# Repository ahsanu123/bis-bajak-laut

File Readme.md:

<p  align="center">    

  <br/>
  <b>Bis Bajak Laut</b> is a Copy of <a href="https://docs.buspirate.com/">Bus Pirate</a>
</p> 

# 🍿 Hardware

## 🌳 Log

- 10 Oktober 2025, 19:30, start date.

## 🧰 References

- [bus pirate hardware documentation](https://docs.buspirate.com/docs/overview/hardware/)

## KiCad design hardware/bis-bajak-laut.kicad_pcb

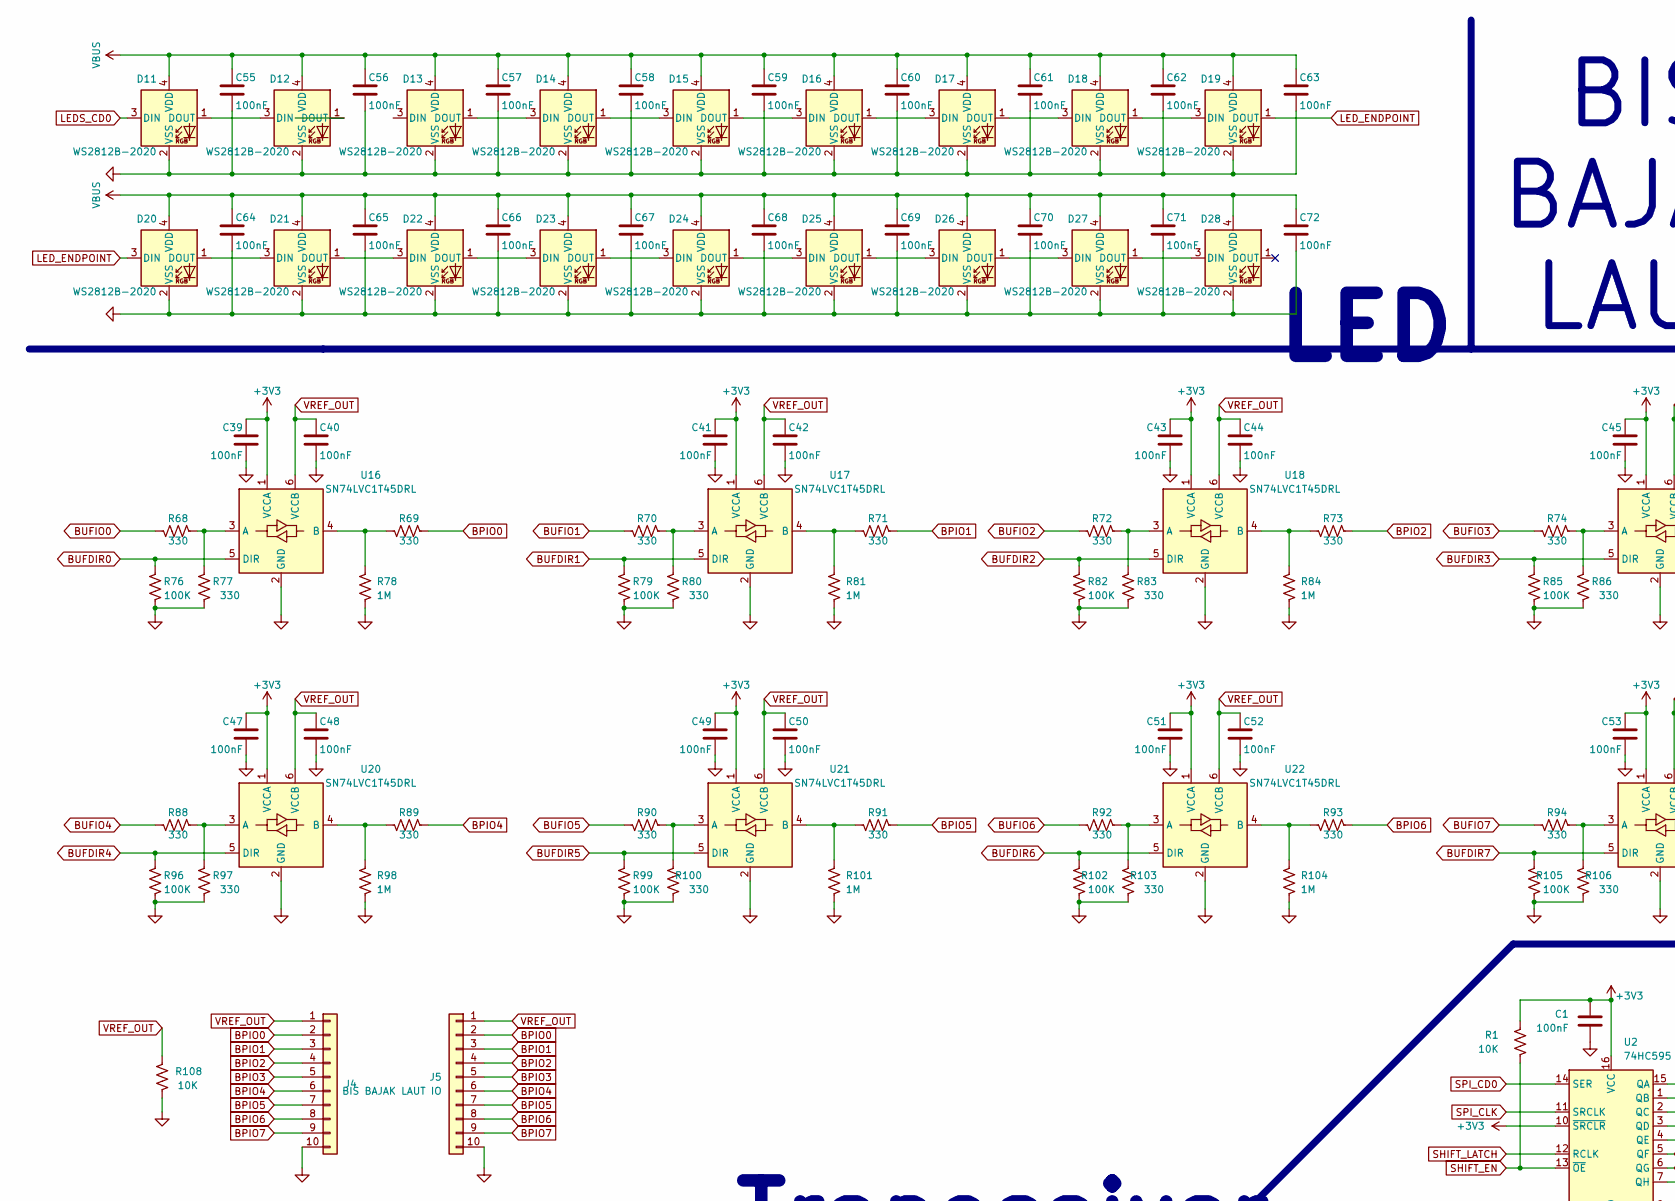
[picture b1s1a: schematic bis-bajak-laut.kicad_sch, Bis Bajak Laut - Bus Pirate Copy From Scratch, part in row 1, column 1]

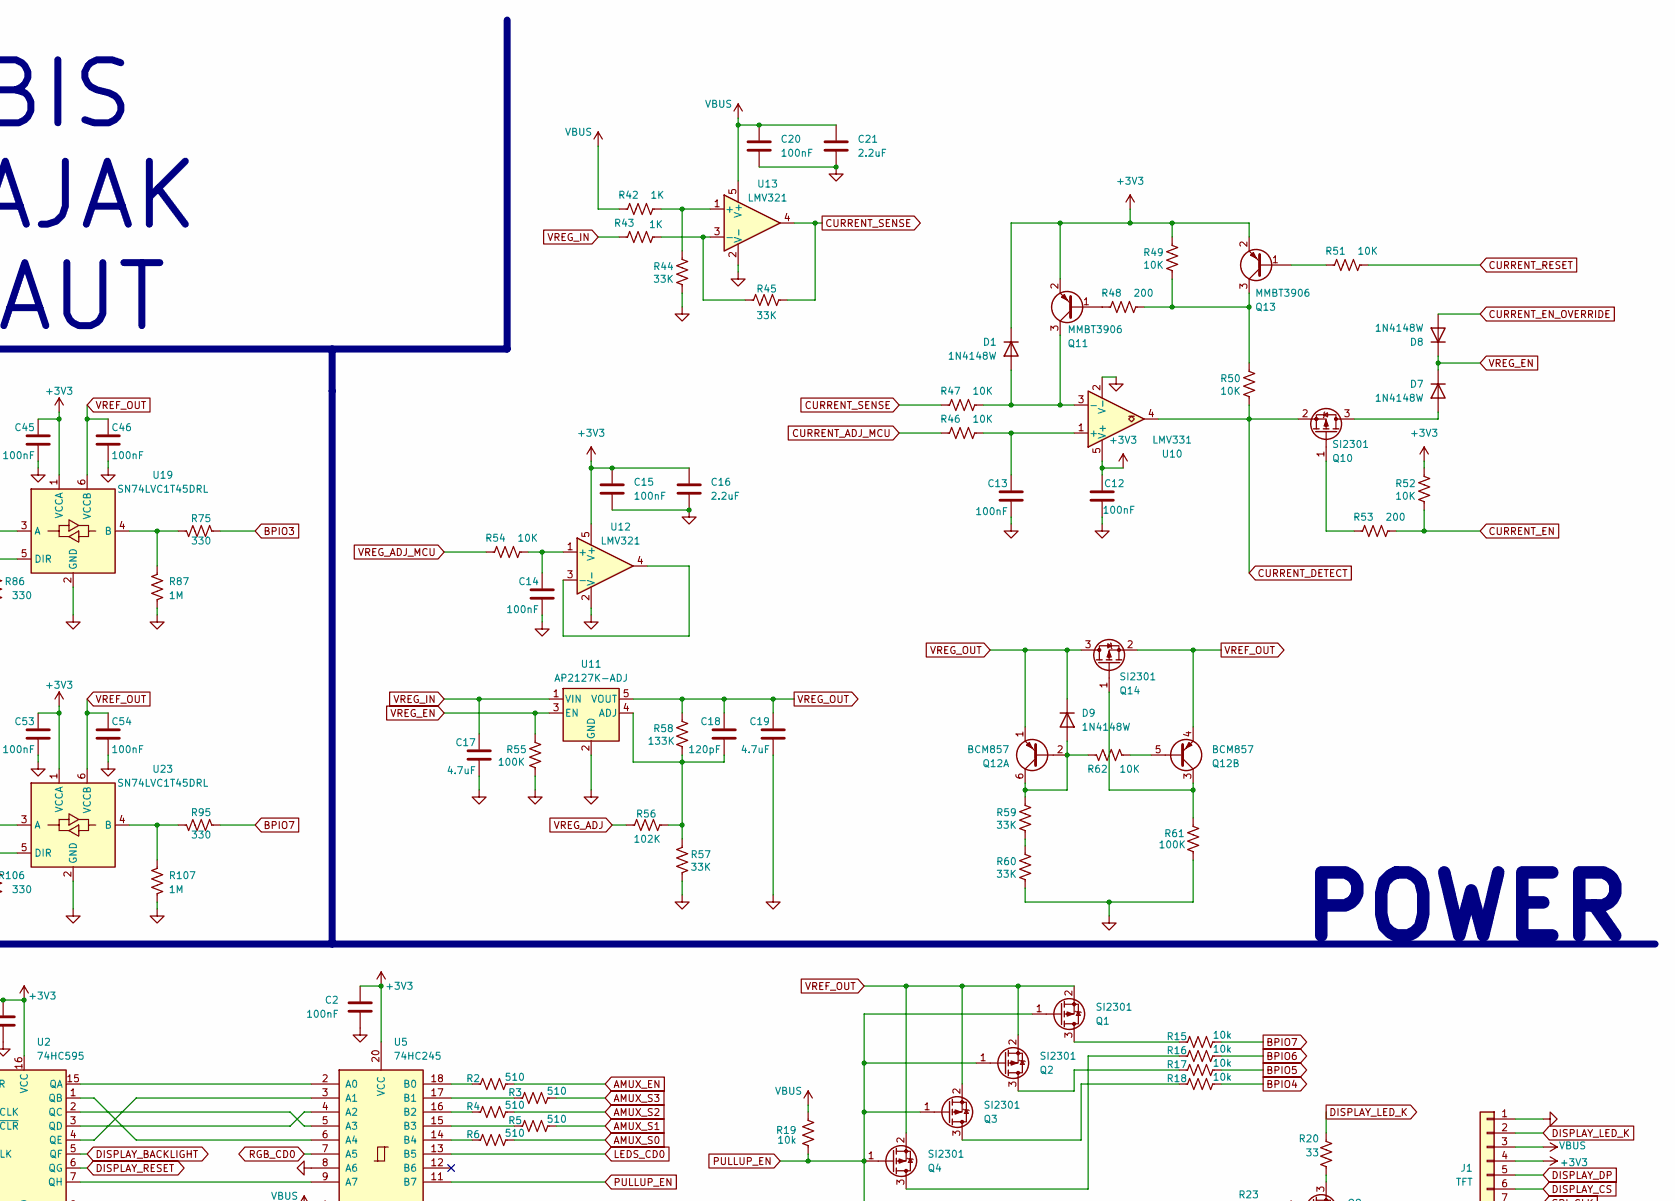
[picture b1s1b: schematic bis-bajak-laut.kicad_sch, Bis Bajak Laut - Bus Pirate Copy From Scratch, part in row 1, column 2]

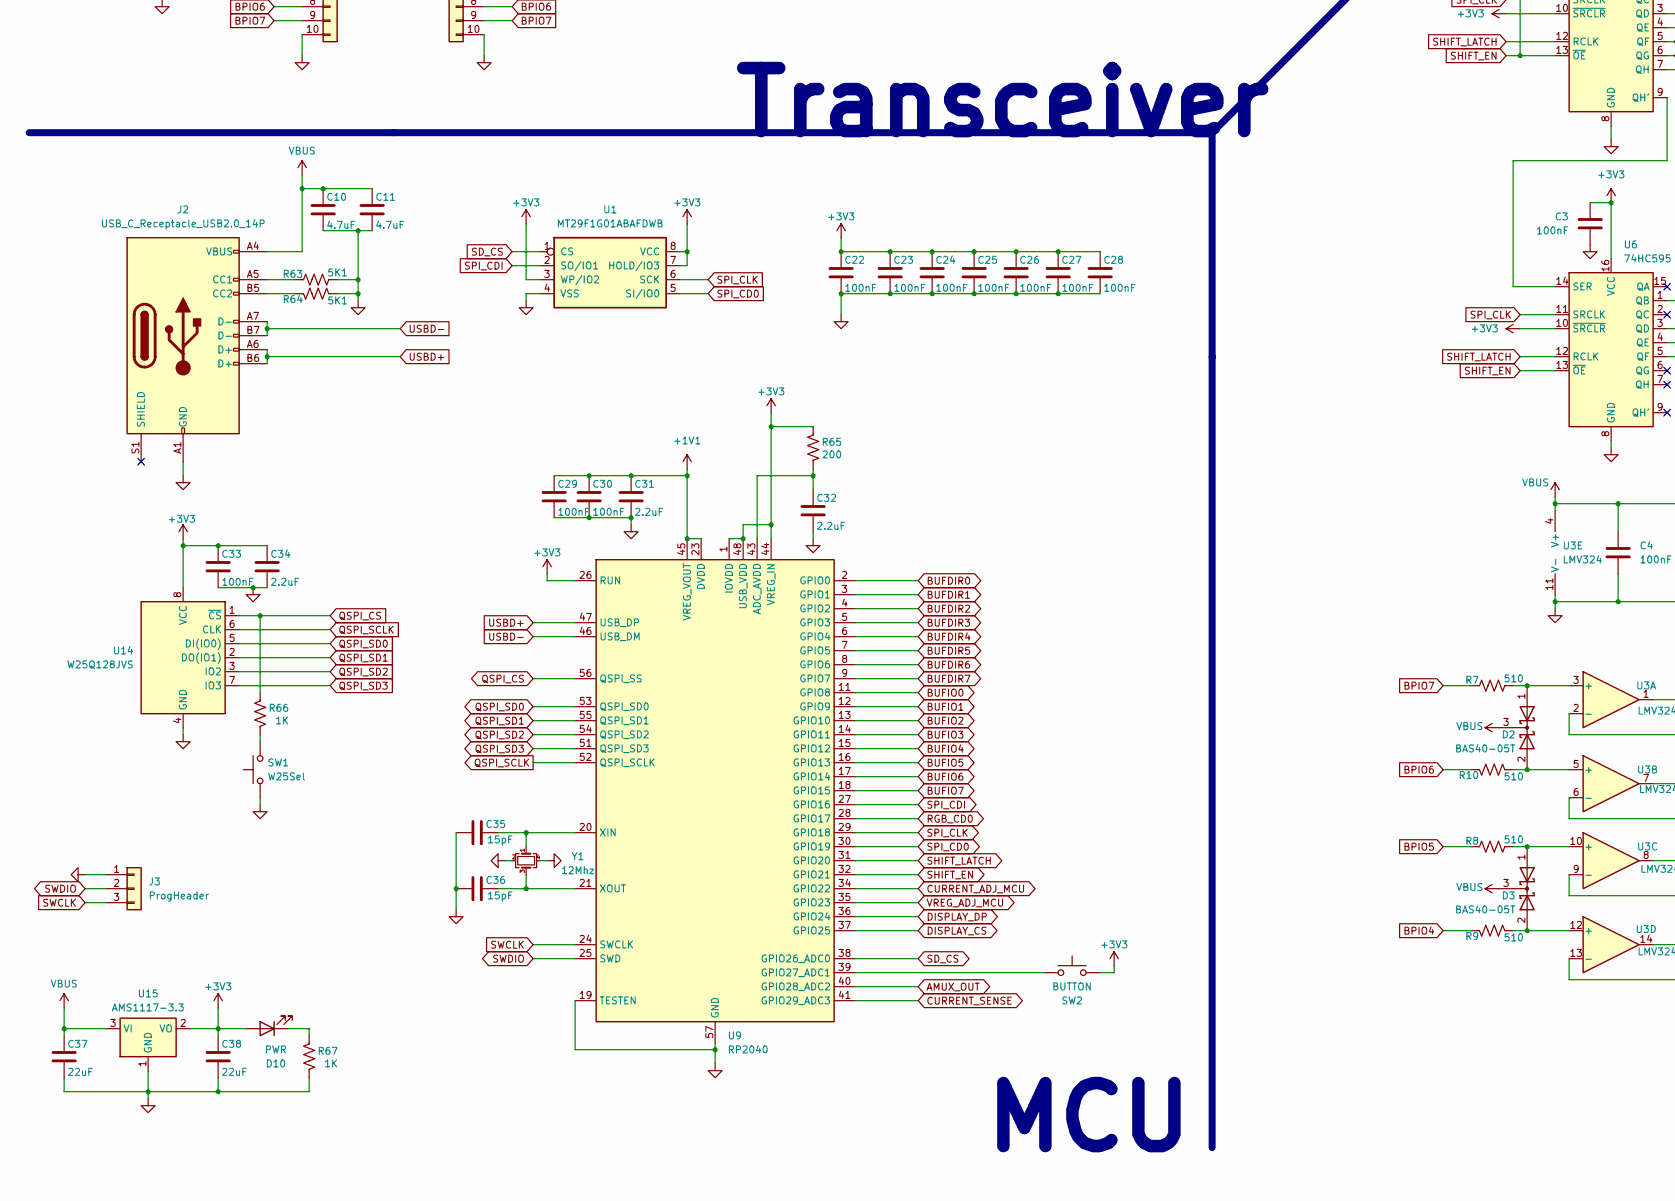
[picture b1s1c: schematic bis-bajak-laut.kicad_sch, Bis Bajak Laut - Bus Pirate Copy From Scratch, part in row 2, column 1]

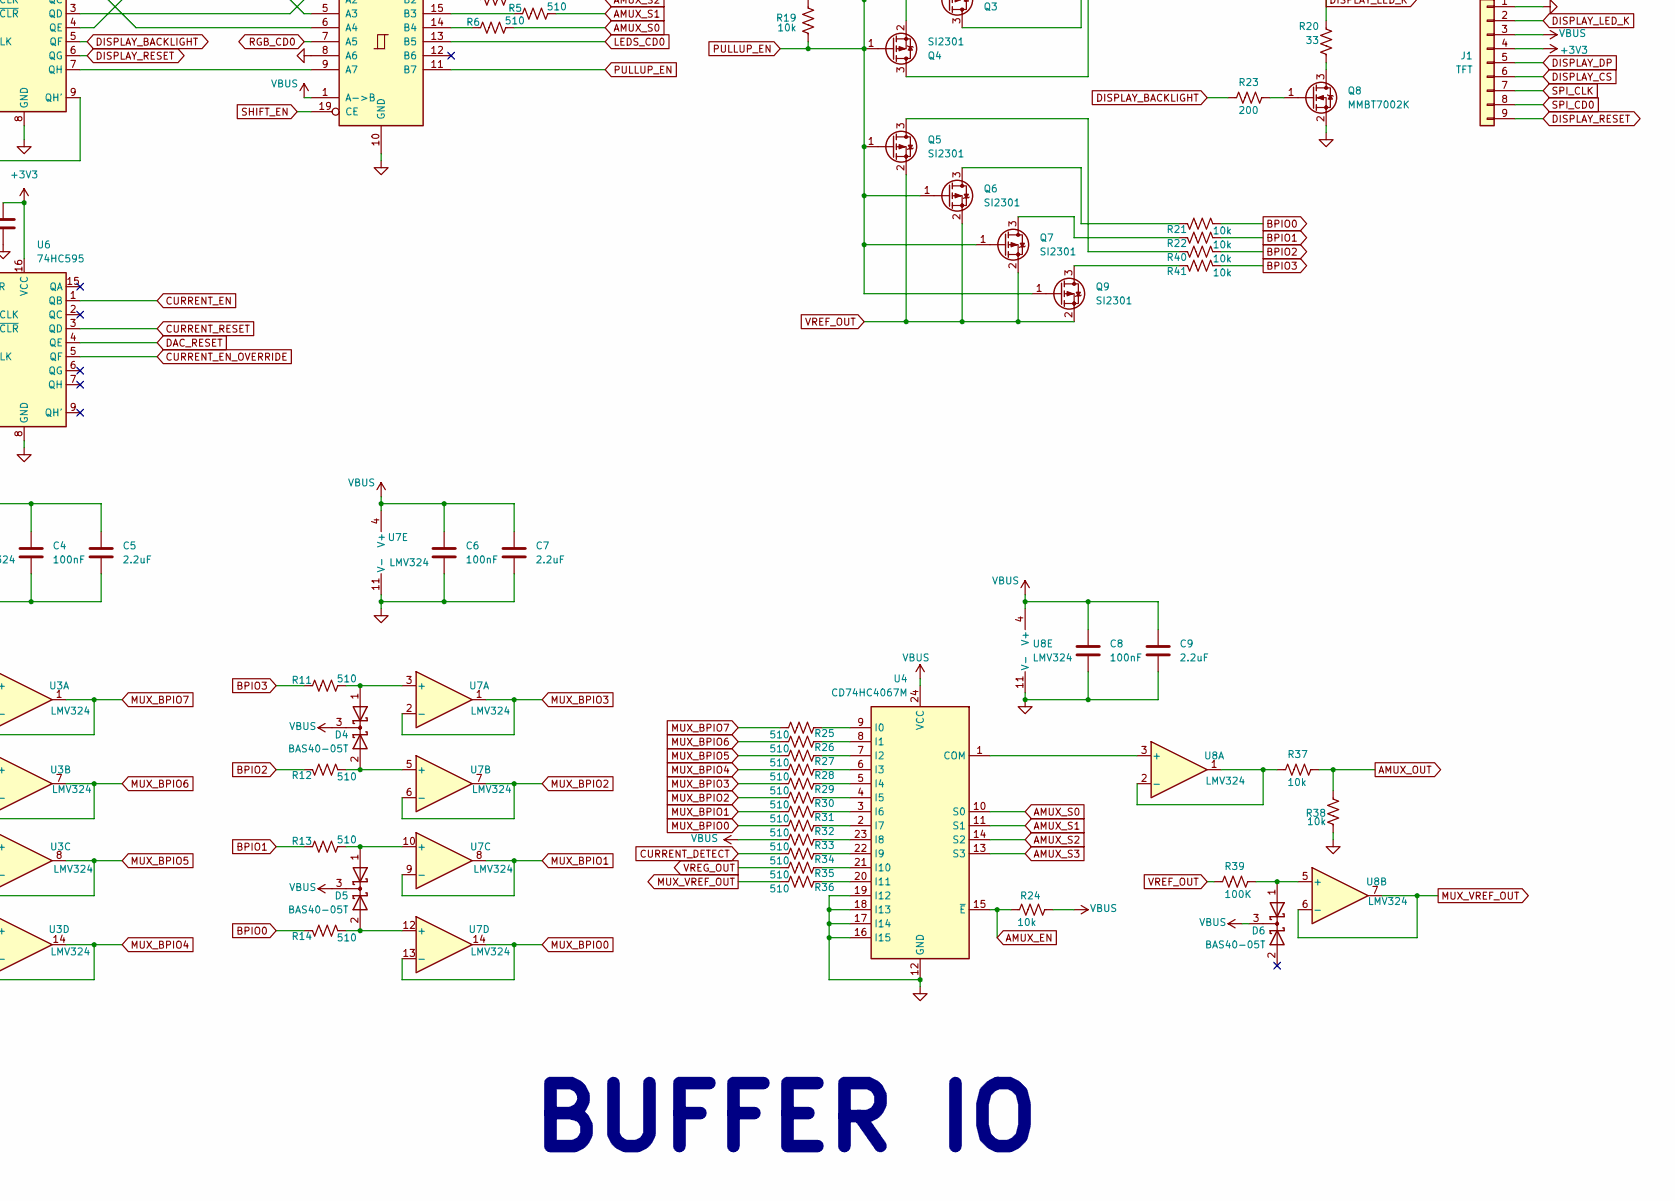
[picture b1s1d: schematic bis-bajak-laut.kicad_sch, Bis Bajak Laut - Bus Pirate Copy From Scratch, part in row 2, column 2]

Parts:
C1, C2, C3, C4, C6, C8, C12, C13, C14, C15, C20, C22, C23, C24, C25, C26, C27, C28, C29, C30, C33, C39, C40, C41, C42, C43, C44, C45, C46, C47, C48, C49, C50, C51, C52, C53, C54, C55, C56, C57, C58, C59, C60, C61, C62, C63, C64, C65, C66, C67, C68, C69, C70, C71, C72: 100nF; C_0805_2012Metric
C5, C7, C9, C16, C21, C31, C32, C34: 2.2uF; C_0805_2012Metric
C10, C11, C17, C19: 4.7uF; C_0805_2012Metric
C18: 120pF; C_0805_2012Metric
C35, C36: 15pF; C_0805_2012Metric
C37, C38: 22uF; C_0805_2012Metric
D1: 1N4148W; D_SOD-123
D2, D3, D4, D5, D6: BAS40-05T; SOT-523
D7, D8, D9: 1N4148W; D_SOD-323
D10: PWR; LED_1206_3216Metric
D11, D12, D13, D14, D15, D16, D17, D18, D19, D20, D21, D22, D23, D24, D25, D26, D27, D28: WS2812B-2020; LED_WS2812B-2020_PLCC4_2.0x2.0mm
J1: TFT; PinSocket_1x09_P2.54mm_Vertical
J2: USB_C_Receptacle_USB2.0_14P; USB_C_Receptacle_GCT_USB4110
J3: ProgHeader; PinSocket_1x03_P2.54mm_Vertical
J4, J5: BIS BAJAK LAUT IO; PinHeader_1x10_P2.54mm_Vertical
Q1, Q2, Q3, Q4, Q5, Q6, Q7, Q9, Q10, Q14: SI2301; SOT-23
Q8: MMBT7002K; SOT-23
Q11, Q13: MMBT3906; SOT-23
Q12: BCM857; SOT-363_SC-70-6_Handsoldering
R1, R46, R47, R49, R50, R51, R52, R54, R62, R108: 10K; R_0805_2012Metric
R2, R3, R4, R5, R6, R7, R8, R9, R10, R11, R12, R13, R14, R25, R26, R27, R28, R29, R30, R31, R32, R33, R34, R35, R36: 510; R_0805_2012Metric
R15, R16, R17, R18, R19, R21, R22, R24, R37, R38, R40, R41: 10k; R_0805_2012Metric
R20: 33; R_0805_2012Metric
R23, R48, R53, R65: 200; R_0805_2012Metric
R39, R55, R61, R76, R79, R82, R85, R96, R99, R102, R105: 100K; R_0805_2012Metric
R42, R43, R66, R67: 1K; R_0805_2012Metric
R44, R45, R57, R59, R60: 33K; R_0805_2012Metric
R56: 102K; R_0805_2012Metric
R58: 133K; R_0805_2012Metric
R63, R64: 5K1; R_0805_2012Metric
R68, R69, R70, R71, R72, R73, R74, R75, R77, R80, R83, R86, R88, R89, R90, R91, R92, R93, R94, R95, R97, R100, R103, R106: 330; R_0805_2012Metric
R78, R81, R84, R87, R98, R101, R104, R107: 1M; R_0805_2012Metric
SW1: W25Sel; SW_Push_1P1T_NO_6x6mm_H9.5mm
SW2: BUTTON; SW_Push_1P1T_NO_6x6mm_H9.5mm
U1: MT29F1G01ABAFDWB; W-PDFN-8-1EP_6x5mm_P1.27mm_EP3x3mm
U2, U6: 74HC595; SOIC-16_3.9x9.9mm_P1.27mm
U3, U7, U8: LMV324; SOIC-14_3.9x8.7mm_P1.27mm
U4: CD74HC4067M; SOIC-24W_7.5x15.4mm_P1.27mm
U5: 74HC245; DIP-20_W8.89mm_SMDSocket_LongPads
U9: RP2040; QFN-56-1EP_7x7mm_P0.4mm_EP3.2x3.2mm
U10: LMV331; SOT-23-5
U11: AP2127K-ADJ; SOT-23-5
U12, U13: LMV321; SOT-23-5
U14: W25Q128JVS; SOIC-8_5.23x5.23mm_P1.27mm
U15: AMS1117-3.3; SOT-223-3_TabPin2
U16, U17, U18, U19, U20, U21, U22, U23: SN74LVC1T45DRL; SOT-563
Y1: 12Mhz; Crystal_SMD_3225-4Pin_3.2x2.5mm_HandSoldering

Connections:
+1V1: C29.1, C30.1, C31.1, U9.23 (DVDD), U9.45 (VREG_VOUT), U9.50 (DVDD)
+3V3: C1.1, C2.1, C3.1, C12.1, C15.1, C16.1, C22.1, C23.1, C24.1, C25.1, C26.1, C27.1, C28.1, C33.1, C34.1, C38.1, C39.1, C41.1, C43.1, C45.1, C47.1, C49.1, C51.1, C53.1, D1.1 (K), D10.2 (A), J1.4, Q11.2 (E), Q13.2 (E), R1.1, R49.1, R52.1, R65.1, SW2.1, U1.3 (WP/IO2), U1.7 (HOLD/IO3), U1.8 (VCC), U2.10 (~SRCLR), U2.16 (VCC), U5.20 (VCC), U6.10 (~SRCLR), U6.16 (VCC), U9.1 (IOVDD), U9.10 (IOVDD), U9.22 (IOVDD), U9.26 (RUN), U9.33 (IOVDD), U9.42 (IOVDD), U9.44 (VREG_IN), U9.48 (USB_VDD), U9.49 (IOVDD), U10.5 (V+), U12.5 (V+), U14.8 (VCC), U15.2 (VO), U16.1 (VCCA), U17.1 (VCCA), U18.1 (VCCA), U19.1 (VCCA), U20.1 (VCCA), U21.1 (VCCA), U22.1 (VCCA), U23.1 (VCCA)
AMUX_EN: R2.2, R24.2, U4.15 (~E)
AMUX_OUT: R37.1, R38.1, U9.40 (GPIO28_ADC2)
AMUX_S0: R6.2, U4.10 (S0)
AMUX_S1: R5.2, U4.11 (S1)
AMUX_S2: R4.2, U4.14 (S2)
AMUX_S3: R3.2, U4.13 (S3)
BPIO0: J4.2, J5.2, R14.1, R21.2, R69.2
BPIO1: J4.3, J5.3, R13.1, R22.2, R71.2
BPIO2: J4.4, J5.4, R12.1, R40.2, R73.2
BPIO3: J4.5, J5.5, R11.1, R41.2, R75.2
BPIO4: J4.6, J5.6, R9.1, R18.2, R89.2
BPIO5: J4.7, J5.7, R8.1, R17.2, R91.2
BPIO6: J4.8, J5.8, R10.1, R16.2, R93.2
BPIO7: J4.9, J5.9, R7.1, R15.2, R95.2
BUFDIR0: R76.1, U9.2 (GPIO0), U16.5 (DIR)
BUFDIR1: R79.1, U9.3 (GPIO1), U17.5 (DIR)
BUFDIR2: R82.1, U9.4 (GPIO2), U18.5 (DIR)
BUFDIR3: R85.1, U9.5 (GPIO3), U19.5 (DIR)
BUFDIR4: R96.1, U9.6 (GPIO4), U20.5 (DIR)
BUFDIR5: R99.1, U9.7 (GPIO5), U21.5 (DIR)
BUFDIR6: R102.1, U9.8 (GPIO6), U22.5 (DIR)
BUFDIR7: R105.1, U9.9 (GPIO7), U23.5 (DIR)
BUFIO0: R68.1, U9.11 (GPIO8)
BUFIO1: R70.1, U9.12 (GPIO9)
BUFIO2: R72.1, U9.13 (GPIO10)
BUFIO3: R74.1, U9.14 (GPIO11)
BUFIO4: R88.1, U9.15 (GPIO12)
BUFIO5: R90.1, U9.16 (GPIO13)
BUFIO6: R92.1, U9.17 (GPIO14)
BUFIO7: R94.1, U9.18 (GPIO15)
CURRENT_ADJ_MCU: R46.2, U9.34 (GPIO22)
CURRENT_DETECT: Q10.2 (S), R34.2, R50.2, U10.4
CURRENT_EN: R52.2, R53.1, U6.1 (QB)
CURRENT_EN_OVERRIDE: D8.2 (A), U6.5 (QF)
CURRENT_RESET: R51.1, U6.3 (QD)
CURRENT_SENSE: R45.2, R47.2, U9.41 (GPIO29_ADC3), U13.4
DAC_RESET: U6.4 (QE)
DISPLAY_BACKLIGHT: R23.2, U2.5 (QF)
DISPLAY_CS: J1.6, U9.37 (GPIO25)
DISPLAY_DP: J1.5, U9.36 (GPIO24)
DISPLAY_LED_K: J1.2, R20.1
DISPLAY_RESET: J1.9, U2.6 (QG)
GND: C1.2, C2.2, C3.2, C4.2, C5.2, C6.2, C7.2, C8.2, C9.2, C10.2, C11.2, C12.2, C13.2, C14.2, C15.2, C16.2, C17.2, C19.2, C20.2, C21.2, C22.2, C23.2, C24.2, C25.2, C26.2, C27.2, C28.2, C29.2, C30.2, C31.2, C32.2, C33.2, C34.2, C35.1, C36.1, C37.2, C38.2, C39.2, C40.2, C41.2, C42.2, C43.2, C44.2, C45.2, C46.2, C47.2, C48.2, C49.2, C50.2, C51.2, C52.2, C53.2, C54.2, C55.2, C56.2, C57.2, C58.2, C59.2, C60.2, C61.2, C62.2, C63.2, C64.2, C65.2, C66.2, C67.2, C68.2, C69.2, C70.2, C71.2, C72.2, D11.2 (VSS), D12.2 (VSS), D13.2 (VSS), D14.2 (VSS), D15.2 (VSS), D16.2 (VSS), D17.2 (VSS), D18.2 (VSS), D19.2 (VSS), D20.2 (VSS), D21.2 (VSS), D22.2 (VSS), D23.2 (VSS), D24.2 (VSS), D25.2 (VSS), D26.2 (VSS), D27.2 (VSS), D28.2 (VSS), J1.1, J2.A1 (GND), J2.A12 (GND), J2.B1 (GND), J2.B12 (GND), J3.1, J4.10, J5.10, Q8.2 (S), R38.2, R44.2, R55.2, R57.2, R60.2, R61.2, R63.2, R64.2, R67.2, R76.2, R77.2, R78.2, R79.2, R80.2, R81.2, R82.2, R83.2, R84.2, R85.2, R86.2, R87.2, R96.2, R97.2, R98.2, R99.2, R100.2, R101.2, R102.2, R103.2, R104.2, R105.2, R106.2, R107.2, R108.2, SW1.1, U1.4 (VSS), U2.8 (GND), U3.11 (V-), U4.12 (GND), U4.16 (I15), U4.17 (I14), U4.18 (I13), U4.19 (I12), U5.8 (A6), U5.10 (GND), U6.8 (GND), U7.11 (V-), U8.11 (V-), U9.19 (TESTEN), U9.57 (GND), U10.2 (V-), U11.2 (GND), U12.2 (V-), U13.2 (V-), U14.4 (GND), U15.1 (GND), U16.2 (GND), U17.2 (GND), U18.2 (GND), U19.2 (GND), U20.2 (GND), U21.2 (GND), U22.2 (GND), U23.2 (GND), Y1.2, Y1.4
LEDS_CD0: D11.3 (DIN), U5.13 (B5)
LED_ENDPOINT: D19.1 (DOUT), D20.3 (DIN)
MUX_BPIO0: R32.2, U7.13 (-), U7.14
MUX_BPIO1: R31.2, U7.8, U7.9 (-)
MUX_BPIO2: R30.2, U7.6 (-), U7.7
MUX_BPIO3: R29.2, U7.1, U7.2 (-)
MUX_BPIO4: R28.2, U3.13 (-), U3.14
MUX_BPIO5: R27.2, U3.8, U3.9 (-)
MUX_BPIO6: R26.2, U3.6 (-), U3.7
MUX_BPIO7: R25.2, U3.1, U3.2 (-)
MUX_VREF_OUT: R36.2, U8.6 (-), U8.7
unnamed: D1.2 (A), Q11.3 (C), R47.1, U10.3 (-)
unnamed: D7.2 (A), Q10.3 (D)
unnamed: D9.2 (A), Q12.2 (B1), Q12.6 (C1), R59.1, R62.2
unnamed: D10.1 (K), R67.1
unnamed: D11.1 (DOUT), D12.3 (DIN)
unnamed: D12.1 (DOUT), D13.3 (DIN)
unnamed: D13.1 (DOUT), D14.3 (DIN)
unnamed: D14.1 (DOUT), D15.3 (DIN)
unnamed: D15.1 (DOUT), D16.3 (DIN)
unnamed: D16.1 (DOUT), D17.3 (DIN)
unnamed: D17.1 (DOUT), D18.3 (DIN)
unnamed: D18.1 (DOUT), D19.3 (DIN)
unnamed: D20.1 (DOUT), D21.3 (DIN)
unnamed: D21.1 (DOUT), D22.3 (DIN)
unnamed: D22.1 (DOUT), D23.3 (DIN)
unnamed: D23.1 (DOUT), D24.3 (DIN)
unnamed: D24.1 (DOUT), D25.3 (DIN)
unnamed: D25.1 (DOUT), D26.3 (DIN)
unnamed: D26.1 (DOUT), D27.3 (DIN)
unnamed: D27.1 (DOUT), D28.3 (DIN)
unnamed: J2.A5 (CC1), R63.1
unnamed: J2.B5 (CC2), R64.1
unnamed: Q1.3 (D), R15.1
unnamed: Q2.3 (D), R17.1
unnamed: Q3.3 (D), R18.1
unnamed: Q4.3 (D), R16.1
unnamed: Q5.3 (D), R40.1
unnamed: Q6.3 (D), R21.1
unnamed: Q7.3 (D), R22.1
unnamed: Q8.3 (D), R20.2
unnamed: Q8.1 (G), R23.1
unnamed: Q9.3 (D), R41.1
unnamed: Q10.1 (G), R53.2
unnamed: Q11.1 (B), R48.2
unnamed: Q12.5 (B2), R62.1
unnamed: Q12.3 (C2), Q14.1 (G), R61.1
unnamed: Q13.1 (B), R51.2
unnamed: Q13.3 (C), R48.1, R49.2, R50.1
unnamed: R59.2, R60.1
unnamed: R66.2, SW1.2
unnamed: U2.15 (QA), U5.2 (A0)
unnamed: U2.1 (QB), U5.6 (A4)
unnamed: U2.2 (QC), U5.5 (A3)
unnamed: U2.3 (QD), U5.4 (A2)
unnamed: U2.4 (QE), U5.3 (A1)
unnamed: U2.9 (QH'), U6.14 (SER)
unnamed: U2.7 (QH), U5.9 (A7)
unnamed: D2.1 (A), R7.2, U3.3 (+)
unnamed: D2.2 (A), R10.2, U3.5 (+)
unnamed: D3.1 (A), R8.2, U3.10 (+)
unnamed: D3.2 (A), R9.2, U3.12 (+)
unnamed: U4.1 (COM), U8.3 (+)
unnamed: R25.1, U4.9 (I0)
unnamed: R26.1, U4.8 (I1)
unnamed: R27.1, U4.7 (I2)
unnamed: R28.1, U4.6 (I3)
unnamed: R29.1, U4.5 (I4)
unnamed: R30.1, U4.4 (I5)
unnamed: R31.1, U4.3 (I6)
unnamed: R32.1, U4.2 (I7)
unnamed: R33.1, U4.23 (I8)
unnamed: R34.1, U4.22 (I9)
unnamed: R35.1, U4.21 (I10)
unnamed: R36.1, U4.20 (I11)
unnamed: R2.1, U5.18 (B0)
unnamed: R3.1, U5.17 (B1)
unnamed: R4.1, U5.16 (B2)
unnamed: R5.1, U5.15 (B3)
unnamed: R6.1, U5.14 (B4)
unnamed: D4.1 (A), R11.2, U7.3 (+)
unnamed: D4.2 (A), R12.2, U7.5 (+)
unnamed: D5.1 (A), R13.2, U7.10 (+)
unnamed: D5.2 (A), R14.2, U7.12 (+)
unnamed: R37.2, U8.1, U8.2 (-)
unnamed: D6.1 (A), R39.1, U8.5 (+)
unnamed: C32.1, R65.2, U9.43 (ADC_AVDD)
unnamed: SW2.2, U9.39 (GPIO27_ADC1)
unnamed: C35.2, U9.20 (XIN), Y1.1
unnamed: C36.2, U9.21 (XOUT), Y1.3
unnamed: C13.1, R46.1, U10.1 (+)
unnamed: C18.2, R56.2, R57.1, R58.2, U11.4 (ADJ)
unnamed: C14.1, R54.1, U12.1 (+)
unnamed: U12.3 (-), U12.4
unnamed: R42.1, R44.1, U13.1 (+)
unnamed: R43.1, R45.1, U13.3 (-)
unnamed: R68.2, R77.1, U16.3 (A)
unnamed: R69.1, R78.1, U16.4 (B)
unnamed: R70.2, R80.1, U17.3 (A)
unnamed: R71.1, R81.1, U17.4 (B)
unnamed: R72.2, R83.1, U18.3 (A)
unnamed: R73.1, R84.1, U18.4 (B)
unnamed: R74.2, R86.1, U19.3 (A)
unnamed: R75.1, R87.1, U19.4 (B)
unnamed: R88.2, R97.1, U20.3 (A)
unnamed: R89.1, R98.1, U20.4 (B)
unnamed: R90.2, R100.1, U21.3 (A)
unnamed: R91.1, R101.1, U21.4 (B)
unnamed: R92.2, R103.1, U22.3 (A)
unnamed: R93.1, R104.1, U22.4 (B)
unnamed: R94.2, R106.1, U23.3 (A)
unnamed: R95.1, R107.1, U23.4 (B)
PULLUP_EN: Q1.1 (G), Q2.1 (G), Q3.1 (G), Q4.1 (G), Q5.1 (G), Q6.1 (G), Q7.1 (G), Q9.1 (G), R19.1, U5.11 (B7)
QSPI_CS: R66.1, U9.56 (QSPI_SS), U14.1 (~CS)
QSPI_SCLK: U9.52 (QSPI_SCLK), U14.6 (CLK)
QSPI_SD0: U9.53 (QSPI_SD0), U14.5 (DI(IO0))
QSPI_SD1: U9.55 (QSPI_SD1), U14.2 (DO(IO1))
QSPI_SD2: U9.54 (QSPI_SD2), U14.3 (IO2)
QSPI_SD3: U9.51 (QSPI_SD3), U14.7 (IO3)
RGB_CD0: U5.7 (A5), U9.28 (GPIO17)
SD_CS: U1.1 (CS), U9.38 (GPIO26_ADC0)
SHIFT_EN: R1.2, U2.13 (~OE), U5.19 (CE), U6.13 (~OE), U9.32 (GPIO21)
SHIFT_LATCH: U2.12 (RCLK), U6.12 (RCLK), U9.31 (GPIO20)
SPI_CD0: J1.8, U1.5 (SI/IO0), U2.14 (SER), U9.30 (GPIO19)
SPI_CDI: U1.2 (SO/IO1), U9.27 (GPIO16)
SPI_CLK: J1.7, U1.6 (SCK), U2.11 (SRCLK), U6.11 (SRCLK), U9.29 (GPIO18)
SWCLK: J3.3, U9.24 (SWCLK)
SWDIO: J3.2, U9.25 (SWD)
USBD+: J2.A6 (D+), J2.B6 (D+), U9.47 (USB_DP)
USBD-: J2.A7 (D-), J2.B7 (D-), U9.46 (USB_DM)
VBUS: C4.1, C5.1, C6.1, C7.1, C8.1, C9.1, C10.1, C11.1, C20.1, C21.1, C37.1, C55.1, C56.1, C57.1, C58.1, C59.1, C60.1, C61.1, C62.1, C63.1, C64.1, C65.1, C66.1, C67.1, C68.1, C69.1, C70.1, C71.1, C72.1, D2.3 (K), D3.3 (K), D4.3 (K), D5.3 (K), D6.3 (K), D11.4 (VDD), D12.4 (VDD), D13.4 (VDD), D14.4 (VDD), D15.4 (VDD), D16.4 (VDD), D17.4 (VDD), D18.4 (VDD), D19.4 (VDD), D20.4 (VDD), D21.4 (VDD), D22.4 (VDD), D23.4 (VDD), D24.4 (VDD), D25.4 (VDD), D26.4 (VDD), D27.4 (VDD), D28.4 (VDD), J1.3, J2.A4 (VBUS), J2.A9 (VBUS), J2.B4 (VBUS), J2.B9 (VBUS), R19.2, R24.1, R33.2, R42.2, U3.4 (V+), U4.24 (VCC), U5.1 (A->B), U7.4 (V+), U8.4 (V+), U13.5 (V+), U15.3 (VI)
VREF_OUT: C40.1, C42.1, C44.1, C46.1, C48.1, C50.1, C52.1, C54.1, J4.1, J5.1, Q1.2 (S), Q2.2 (S), Q3.2 (S), Q4.2 (S), Q5.2 (S), Q6.2 (S), Q7.2 (S), Q9.2 (S), Q12.4 (E2), Q14.2 (S), R39.2, R108.1, U16.6 (VCCB), U17.6 (VCCB), U18.6 (VCCB), U19.6 (VCCB), U20.6 (VCCB), U21.6 (VCCB), U22.6 (VCCB), U23.6 (VCCB)
VREG_ADJ: R56.1
VREG_ADJ_MCU: R54.2, U9.35 (GPIO23)
VREG_EN: D7.1 (K), D8.1 (K), R55.1, U11.3 (EN)
VREG_IN: C17.1, R43.2, U11.1 (VIN)
VREG_OUT: C18.1, C19.1, D9.1 (K), Q12.1 (E1), Q14.3 (D), R35.2, R58.1, U11.5 (VOUT)

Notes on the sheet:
Transceiver
LED
BIS BAJAK LAUT
BUFFER IO
MCU
POWER

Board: 2 copper layers, 253 parts (1 on the bottom side), 180 nets, no tracks yet.

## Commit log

2025-10-08 feat: bis bajak laut initial commit
2025-10-08 feat: copying schematic part 1
2025-10-08 chore: add logo and update readme
    Update Readme.md
2025-10-09 feat: copying schematic part 2
2025-10-09 feat: finish copying schematic
2025-10-09 feat: match footprint
2025-10-09 feat: create pcb
2025-10-10 feat: component arrangement progress 1
